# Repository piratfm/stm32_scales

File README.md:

# STM32 scales

Software and hardware for child weight meter (scales) with glass LCD display
Based on branded Chicco weight meter model # 8312.60.001

Due original "brains" PCB became broken for some reason (operational amplifier burned-out, and scales always shows zeroes), the decision to replace
it by STM32 is made. As additional "pro", scales precision has been 10x increased, comparing to original "brains" of scales.

## Original parts that been used:
 * load sensors bridge (3 pins each).
 * original 5 symbol glass LCD display.
 * original plastic enclosure with pushbuttons.

## Used hardware:
 * HX711 ADC
 * STM32F103C8T6 as MCU and software-base LCD controller (by using RTC interrupts)
 
 schematic of the board: [schematic](https://github.com/piratfm/stm32_scales/blob/master/hardware/weightmeter_schematic.pdf)

## To calibrate:
 1. Put weight meter into the flat table (without any load).
 2. Press "tare" button when powering-on device (press both buttons, tare and power).
 3. You will see some 5-digit number, this is initial ADC value without scale.
 4. When You see "10.000" on display, put 10.000 Kg reference load onto weight meter.
 5. You will see some 5-digit number again, but a little bit higher, this is ADC value with load and without scale.
 6. Then You will see 4-digit number in range 35...300. This is calculated "scale" value for calibration, that number will be saved into flash.
 7. Done, Your weight meter is now calibrated and displays correct value in Kg.

## To measure:
 1. Turn on scales.
 2. Wait until it shows 00000.
 3. Put load into the scales and wait until triangle appears on display.
 4. There will be actual measured weight (in average mode), so even if kid is moving, the scales are still show precise value.
 5. After some time, the weight amount will blink and keeps displayed even if load is removed (memory function).
 6. After some time more, scales turns off automatically.

## Power consumption:
Active mode: 6 mA
Power down mode: 20 uA

License: GPL

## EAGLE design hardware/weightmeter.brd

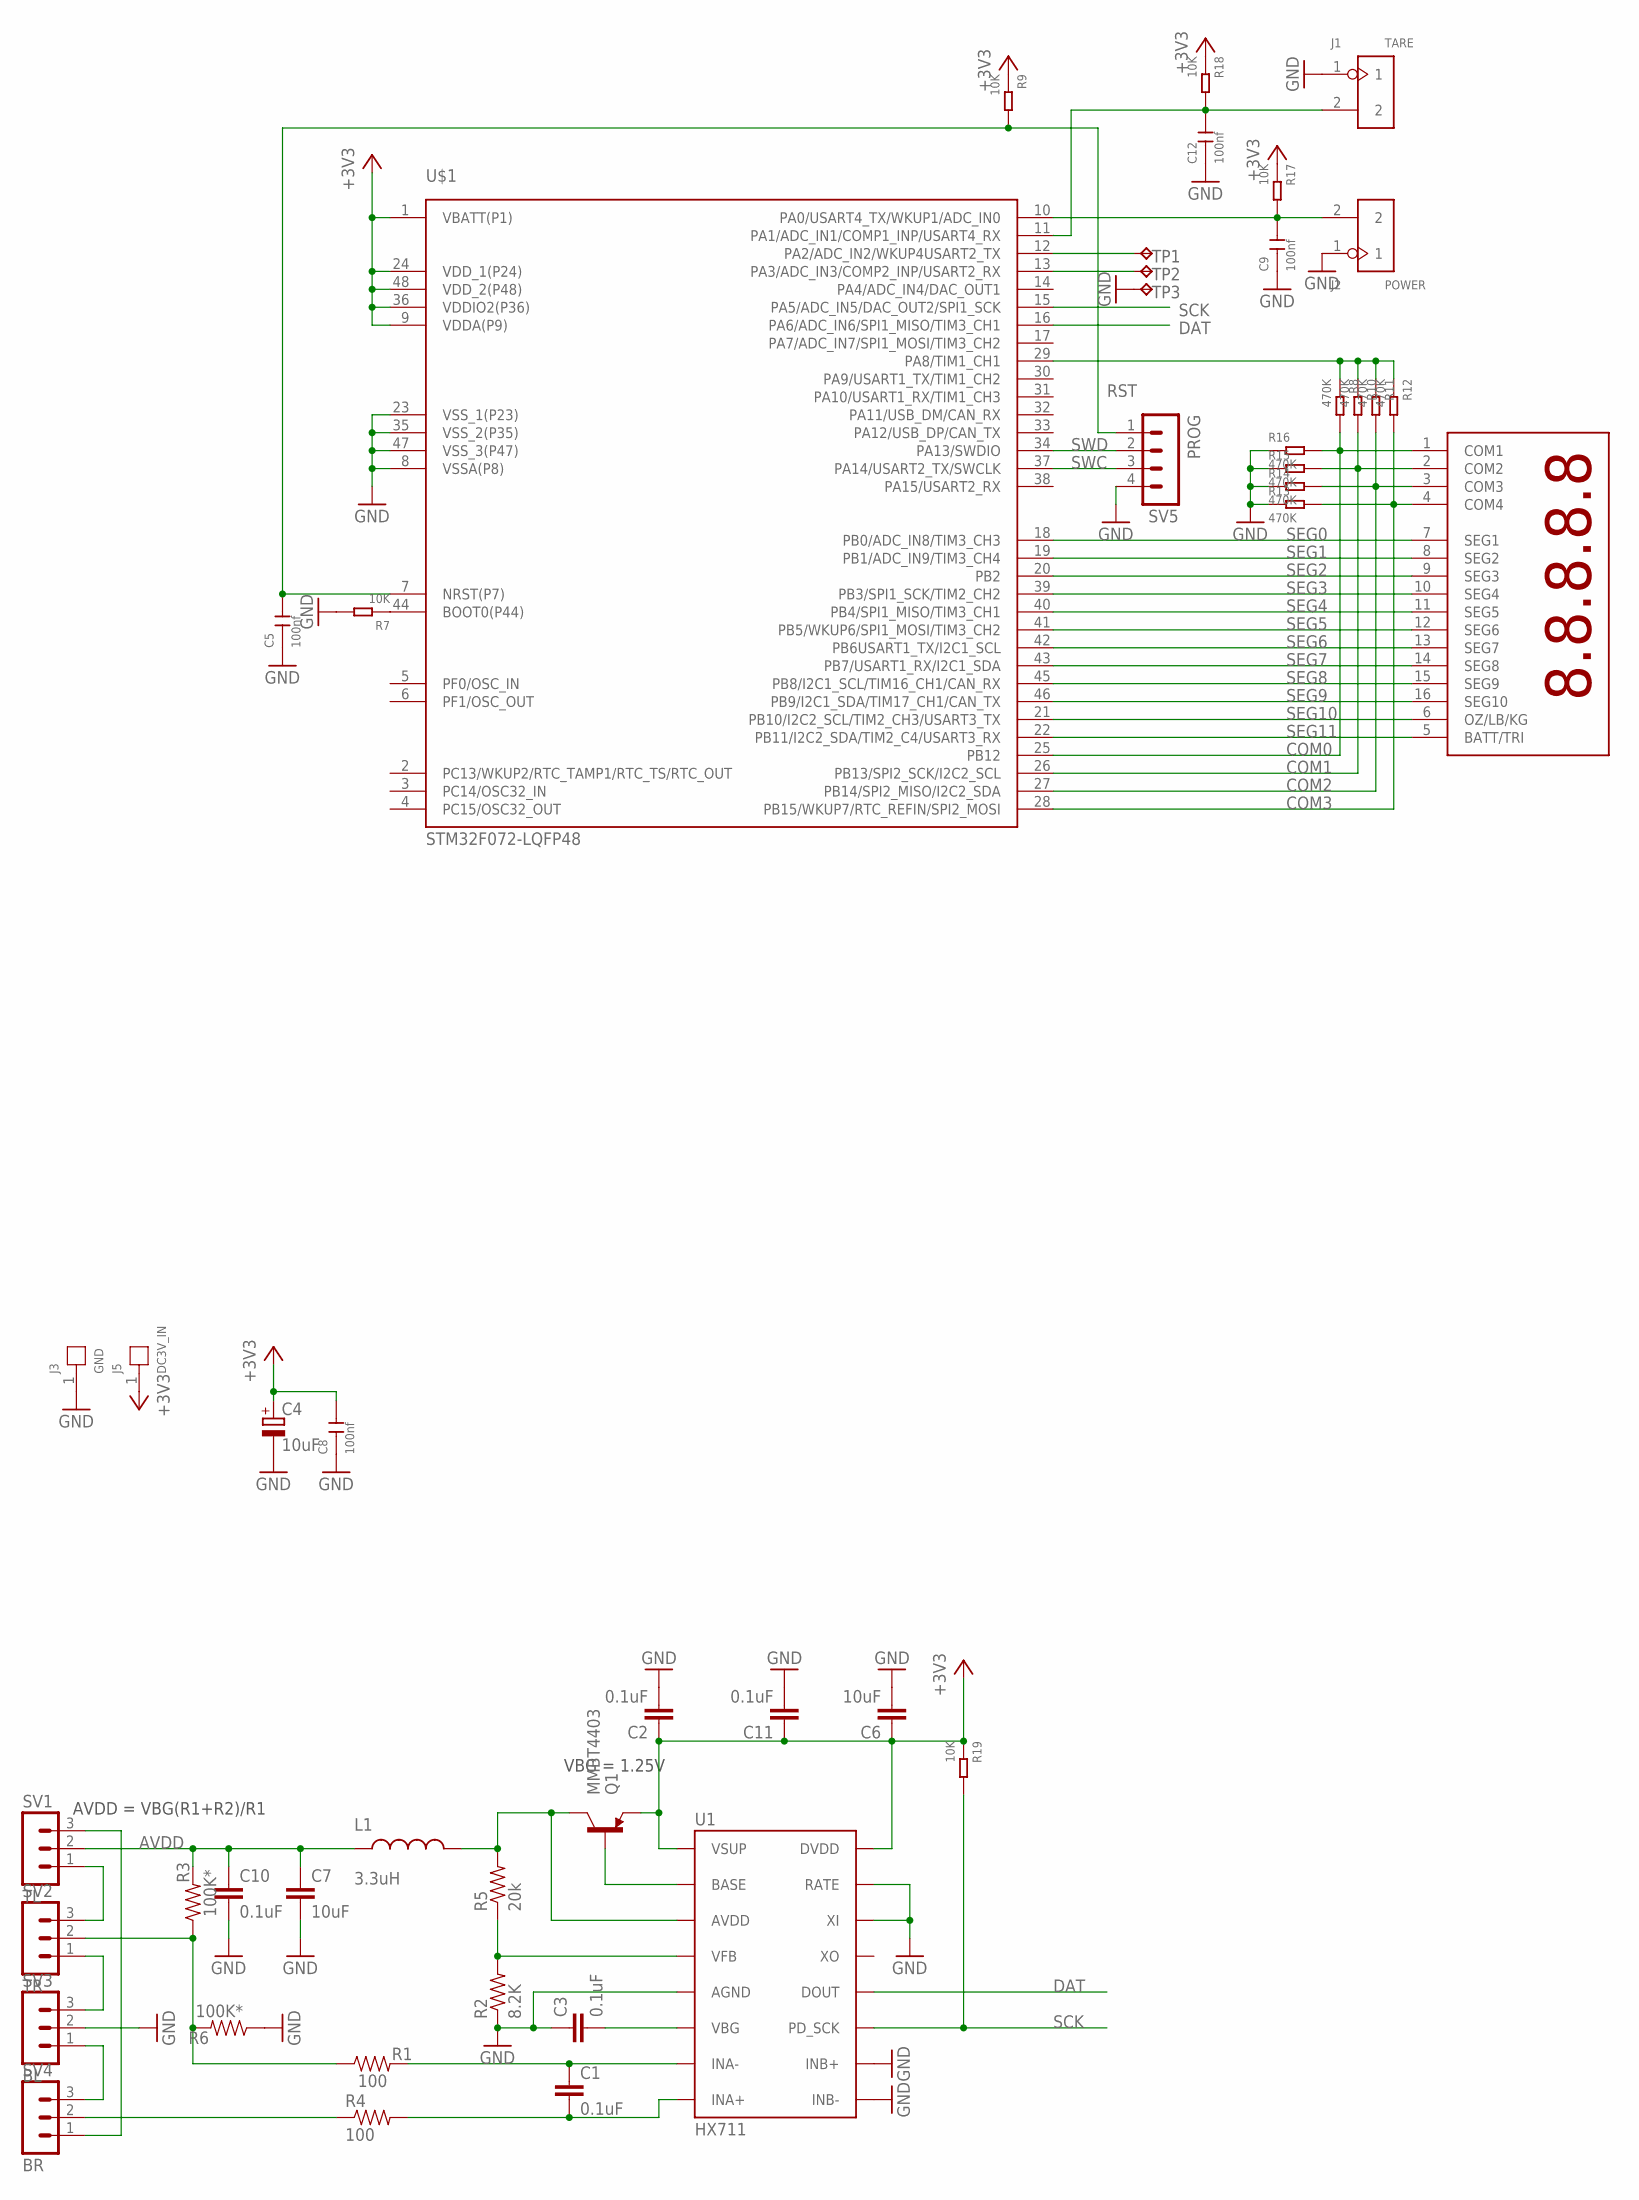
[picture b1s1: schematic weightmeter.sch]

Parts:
C1, C2, C3, C10, C11: 0.1uF; 0603-CAP
C4: 10uF; A/3216-18R
C5, C8, C9, C12: 100nf; C0805
C6, C7: 10uF; 1210
J1: TARE; H2-2.54
J2: POWER; H2-2.54
J3: GND; 1P-65/35MIL
J5: DC3V_IN; 1P-65/35MIL
L1: 3.3uH; 0805
Q1: MMBT4403; SOT23-3
R1, R4: 100; 0603-RES
R2: 8.2K; 0603-RES
R3, R6: 100K*; 0603-RES
R5: 20k; 0603-RES
R7, R9, R17, R18, R19: 10K; R0805
R8, R10, R11, R12, R13, R14, R15, R16: 470K; R0805
SV1: TL; MA03-1
SV2: TR; MA03-1
SV3: BL; MA03-1
SV4: BR; MA03-1
SV5: PROG; MA04-1
TP1, TP2, TP3: UART_OUT; B1,27
U1: HX711; SO16
U$1: STM32F072-LQFP48; LQFP48
X1: 1296-T08; 1296-08

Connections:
+3V3: C2.1, C4.+, C6.1, C8.2, C11.1, J5.1, Q1.2 (E), R9.1, R17.1, R18.1, R19.1, U1.1 (VSUP), U1.16 (DVDD), U$1.1 (VBATT(P1)), U$1.9 (VDDA(P9)), U$1.24 (VDD_1(P24)), U$1.36 (VDDIO2(P36)), U$1.48 (VDD_2(P48))
A+: R4.1, SV4.2
A-: R1.1, R3.1, R6.2, SV2.2
AVDD: C7.1, C10.1, L1.1, R3.2, SV1.2
COM0: R8.2, R16.2, U$1.25 (PB12), X1.1 (COM1)
COM1: R10.2, R15.2, U$1.26 (PB13/SPI2_SCK/I2C2_SCL), X1.2 (COM2)
COM2: R11.2, R14.2, U$1.27 (PB14/SPI2_MISO/I2C2_SDA), X1.3 (COM3)
COM3: R12.2, R13.2, U$1.28 (PB15/WKUP7/RTC_REFIN/SPI2_MOSI), X1.4 (COM4)
DAT: U1.12 (DOUT), U$1.16 (PA6/ADC_IN6/SPI1_MISO/TIM3_CH1)
GND: C2.2, C3.1, C4.-, C5.1, C6.2, C7.2, C8.1, C9.1, C10.2, C11.2, C12.1, J1.1, J2.1, J3.1, R2.1, R6.1, R7.2, R13.1, R14.1, R15.1, R16.1, SV3.2, SV5.4, TP3.TP, U1.5 (AGND), U1.9 (INB-), U1.10 (INB+), U1.14 (XI), U1.15 (RATE), U$1.8 (VSSA(P8)), U$1.23 (VSS_1(P23)), U$1.35 (VSS_2(P35)), U$1.47 (VSS_3(P47))
unnamed: SV1.1, SV2.3
unnamed: SV2.1, SV3.3
unnamed: SV3.1, SV4.3
unnamed: SV1.3, SV4.1
unnamed: Q1.1 (B), U1.2 (BASE)
unnamed: R2.2, R5.1, U1.4 (VFB)
unnamed: C3.2, U1.6 (VBG)
unnamed: L1.2, Q1.3 (C), R5.2, U1.3 (AVDD)
unnamed: TP1.TP, U$1.12 (PA2/ADC_IN2/WKUP4USART2_TX)
unnamed: C1.1, R1.2, U1.7 (INA-)
unnamed: C1.2, R4.2, U1.8 (INA+)
unnamed: TP2.TP, U$1.13 (PA3/ADC_IN3/COMP2_INP/USART2_RX)
unnamed: C12.2, J1.2, R18.2, U$1.11 (PA1/ADC_IN1/COMP1_INP/USART4_RX)
unnamed: R7.1, U$1.44 (BOOT0(P44))
unnamed: C9.2, J2.2, R17.2, U$1.10 (PA0/USART4_TX/WKUP1/ADC_IN0)
unnamed: R8.1, R10.1, R11.1, R12.1, U$1.29 (PA8/TIM1_CH1)
RST: C5.2, R9.2, SV5.1, U$1.7 (NRST(P7))
SCK: R19.2, U1.11 (PD_SCK), U$1.15 (PA5/ADC_IN5/DAC_OUT2/SPI1_SCK)
SEG0: U$1.18 (PB0/ADC_IN8/TIM3_CH3), X1.7 (SEG1)
SEG1: U$1.19 (PB1/ADC_IN9/TIM3_CH4), X1.8 (SEG2)
SEG2: U$1.20 (PB2), X1.9 (SEG3)
SEG3: U$1.39 (PB3/SPI1_SCK/TIM2_CH2), X1.10 (SEG4)
SEG4: U$1.40 (PB4/SPI1_MISO/TIM3_CH1), X1.11 (SEG5)
SEG5: U$1.41 (PB5/WKUP6/SPI1_MOSI/TIM3_CH2), X1.12 (SEG6)
SEG6: U$1.42 (PB6USART1_TX/I2C1_SCL), X1.13 (SEG7)
SEG7: U$1.43 (PB7/USART1_RX/I2C1_SDA), X1.14 (SEG8)
SEG8: U$1.45 (PB8/I2C1_SCL/TIM16_CH1/CAN_RX), X1.15 (SEG9)
SEG9: U$1.46 (PB9/I2C1_SDA/TIM17_CH1/CAN_TX), X1.16 (SEG10)
SEG10: U$1.21 (PB10/I2C2_SCL/TIM2_CH3/USART3_TX), X1.6 (OZ/LB/KG)
SEG11: U$1.22 (PB11/I2C2_SDA/TIM2_C4/USART3_RX), X1.5 (BATT/TRI)
SWC: SV5.3, U$1.37 (PA14/USART2_TX/SWCLK)
SWD: SV5.2, U$1.34 (PA13/SWDIO)

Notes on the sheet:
VBG = 1.25V
AVDD = VBG(R1+R2)/R1

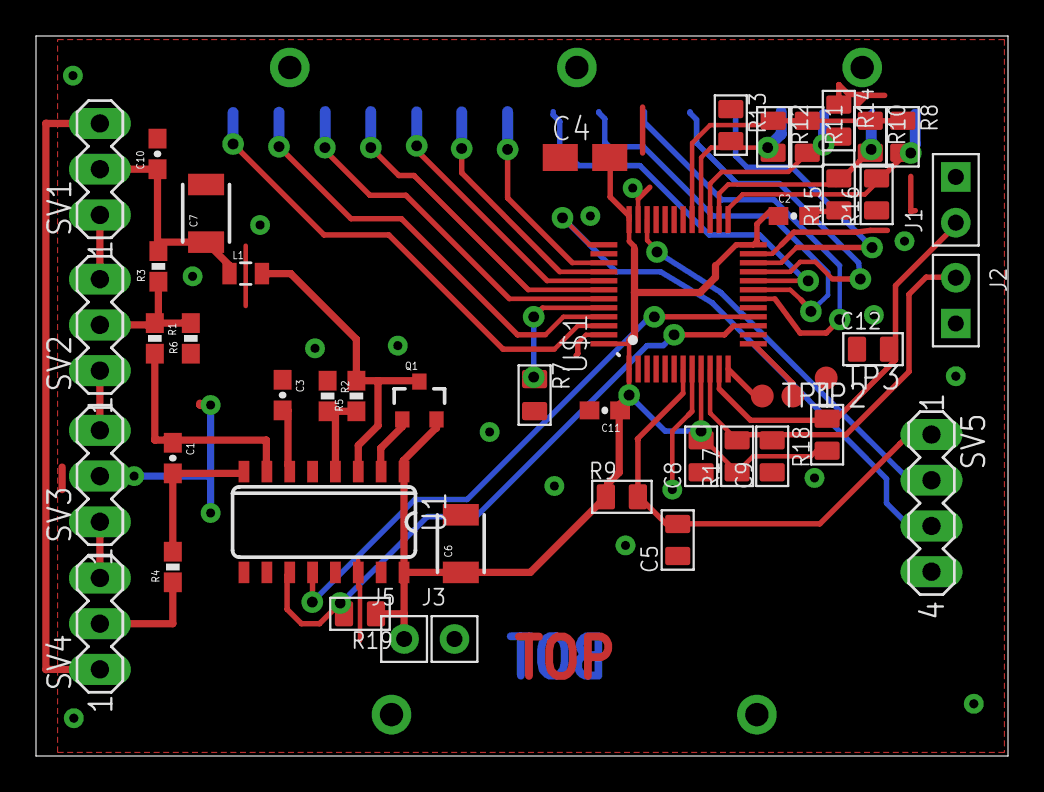
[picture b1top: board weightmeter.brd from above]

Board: 2 copper layers, 54.0 x 40.0 mm, 48 parts (1 on the bottom side), 42 nets.

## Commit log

2017-09-15 initial release. Fix minimal scale to 35.
2017-09-15 update readme.
2017-09-18 increase granularity of scale
2017-09-19 fix power off. Higher gain.
2017-12-21 Enchance scales logic (more averaging).

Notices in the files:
parts and their libraries:
SparkFun-DiscreteSemi: Licensing: Creative Commons ShareAlike 4.0 International - https://creativecommons.org/licenses/by-sa/4.0
SparkFun-Aesthetics: Licensing: CC v3.0 Share-Alike You are welcome to use this library for commercial purposes.
